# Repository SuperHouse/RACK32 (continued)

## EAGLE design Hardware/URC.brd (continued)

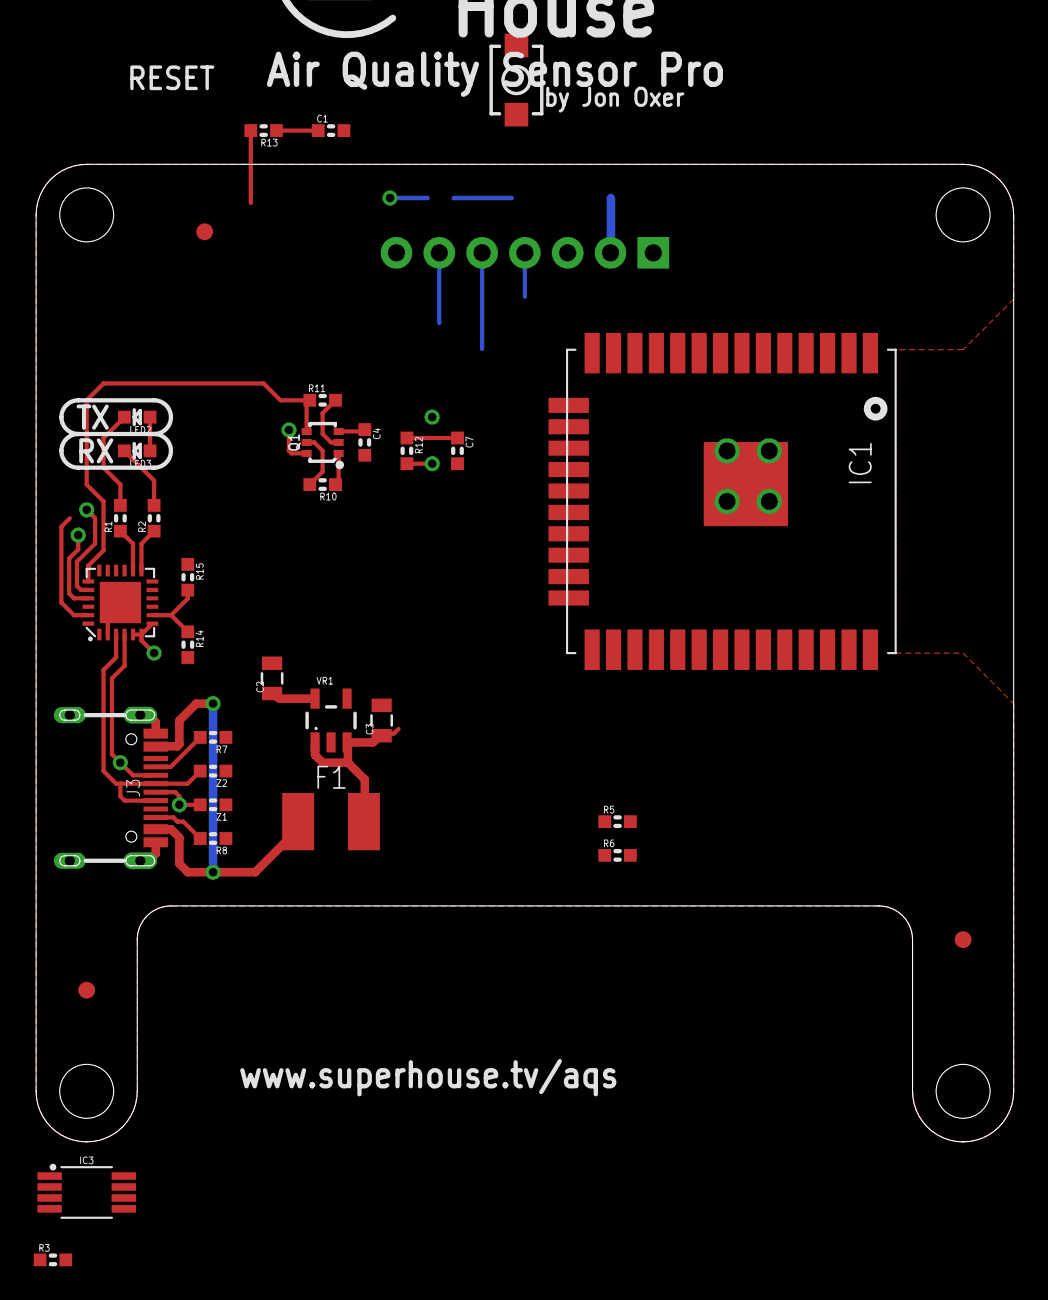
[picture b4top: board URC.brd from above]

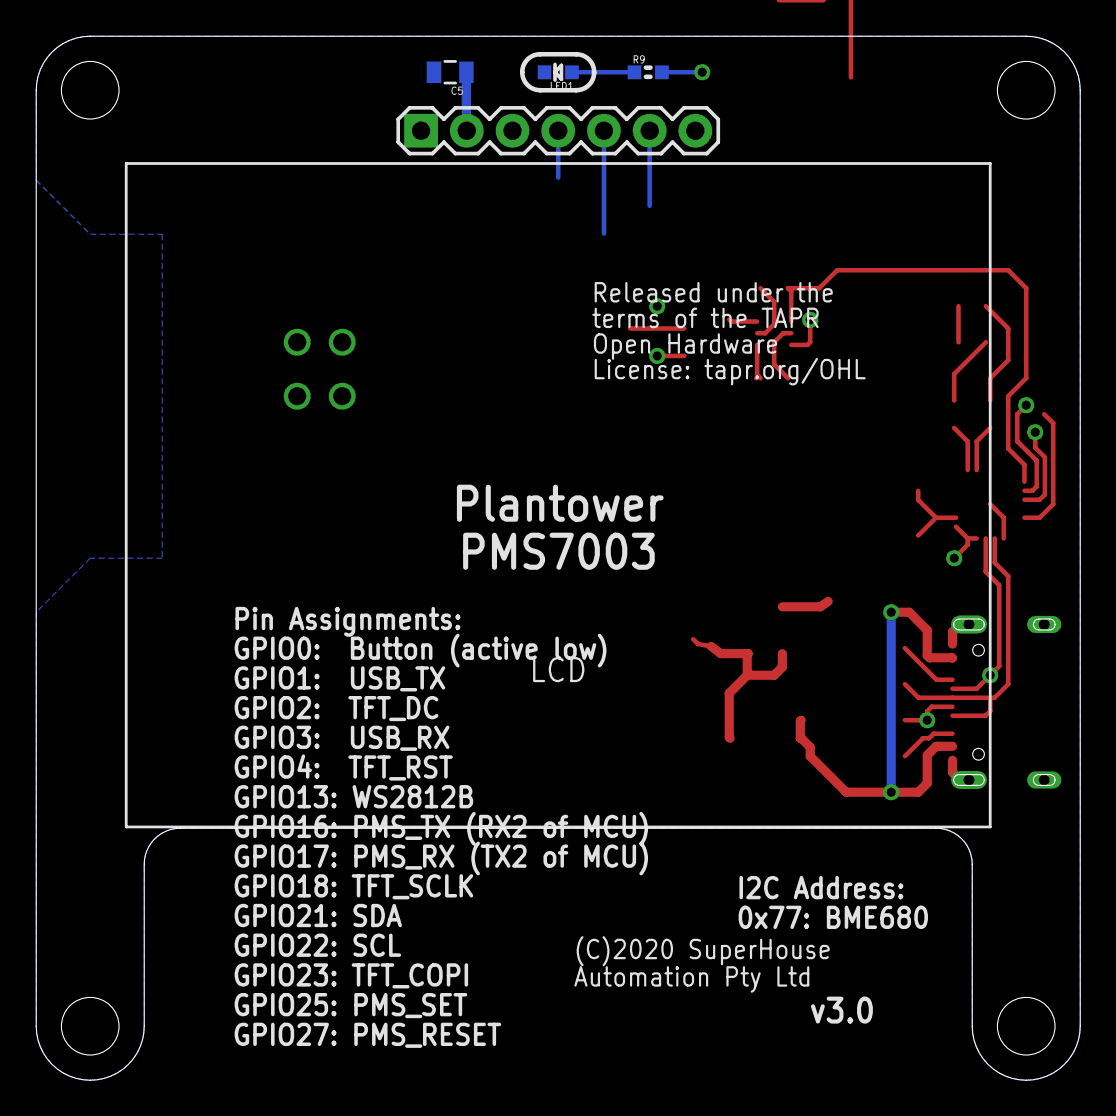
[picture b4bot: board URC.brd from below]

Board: 2 copper layers, 58.0 x 58.0 mm, 37 parts (4 on the bottom side), 28 nets.

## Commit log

2021-06-20 Initial import of project files.
2021-07-27 Created ESP32 version of URC controller. v1.0 release
2021-07-27 Added notes about LCD.
2021-07-27 Rough start of passthrough version of URC controller.
2021-07-27 Added Keynote file for experimenting with layouts.
2021-07-27 Deleted obsolete files.
2021-07-27 Added render of ESP32 version.
2021-07-27 Schematic progress for passthrough edition.
2021-07-27 Created LCD breakout. ERC and DRC for v1.0 release.
2021-07-28 Major mechanical shrinkage for revised v1.0 release.
2021-07-28 Tie unused inputs to GND.
2021-07-28 Renamed LCD board files because they're not specific to the URC.
2021-07-28 Added I/O header with spare pins for I2C port 2 and serial port 2.
2021-07-29 Added dimensions and generated PDF of measurements.
2021-07-29 Fixed pin allocation notes and labels in schematic. Renamed mechanical PDF to clarify its purpose. Generated schematic PDF.
2021-07-29 Added Fusion360 and STL models of the ESP32 version of the controller.
2021-07-29 Moved drawings and 3D files into Mechanical folder, and added Aaron's dimensional drawing.
2021-07-30 Added F3D and STEP files. Removed STL. Added PDF of TFTBR dimensions.
2021-08-09 Added miscellaneous images of case concepts and boards.
2021-08-09 Added usb v2 version of passthrough board.
2021-08-09 Minor updates to boards.
2021-08-09 Deleted files that are also in the URC repo.
2021-08-09 Renamed board files to match new project name.
2021-08-09 Modified ReadMe to suit RACK32 instead of URC.
2021-09-20 Changed PTC to 1206 size. Replaced power LED header.
2021-09-20 Added backpower protection for PoE module.
2021-09-20 Added link to OXRS.
2021-09-22 Added link to OXRS.io on the silkscreen. Connected second SD card detect pad to GND for improved mechanical strength.
2021-10-24 Add files via upload
    adding BOM files
2021-12-15 Library updates and routing improvements.
